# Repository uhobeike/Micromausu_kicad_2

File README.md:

# Micromausu_kicad_2
# move repository
## [InvetHub](https://inventhub.io/beike/Micromausu_2/tree/master/gekko?repoId=5f508c41b8c69c54c1f2025a&dirHash=&hash=25df0beb9022b2a77b5f545d1a530aec806a017b&path=gekko&size=undefined&isGitHub=true)

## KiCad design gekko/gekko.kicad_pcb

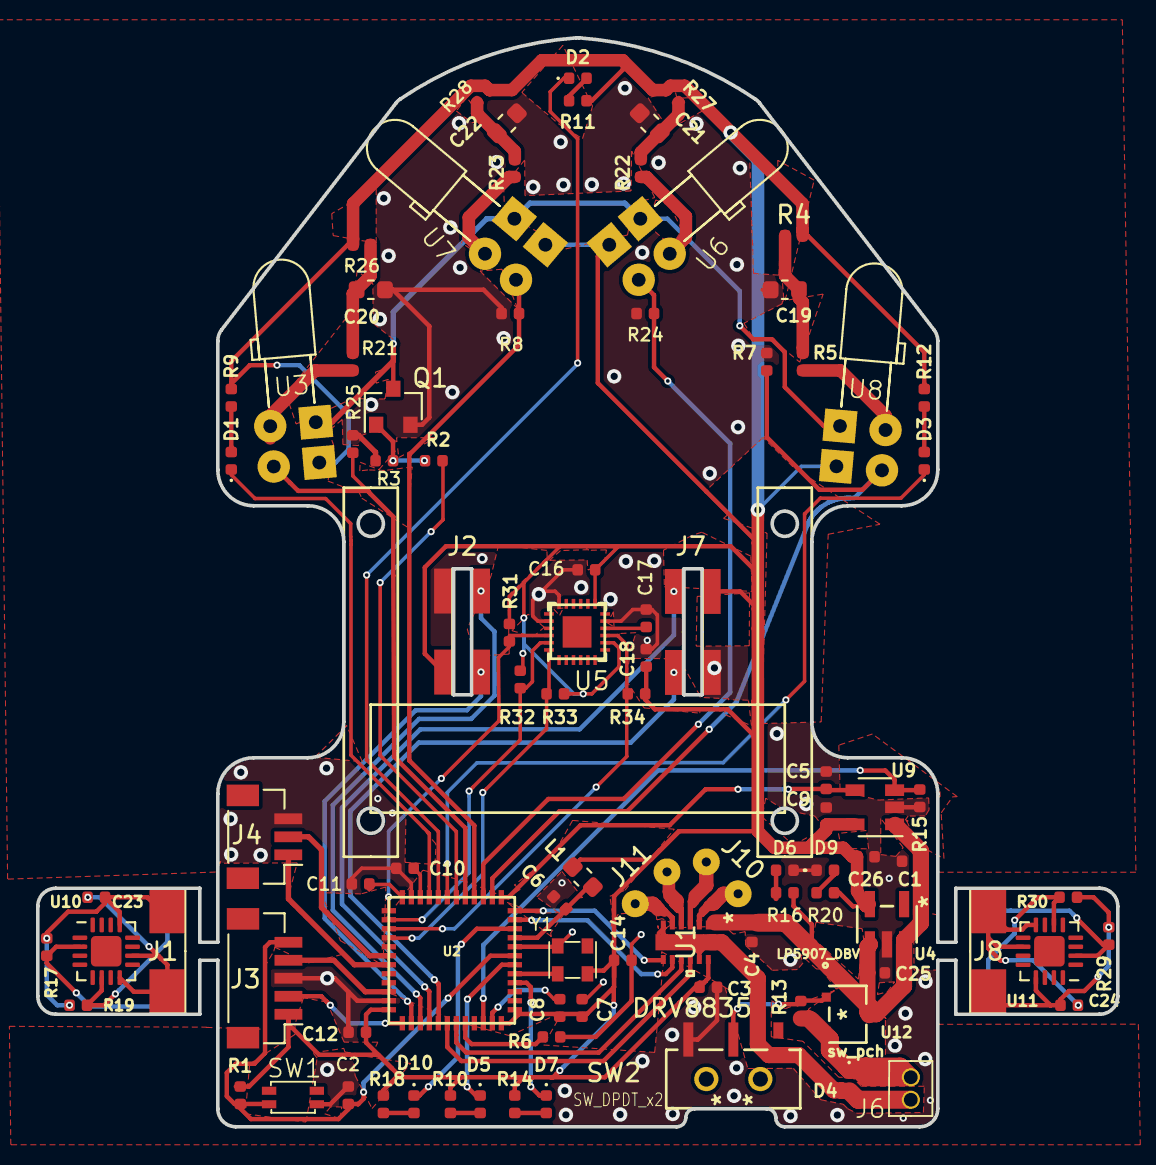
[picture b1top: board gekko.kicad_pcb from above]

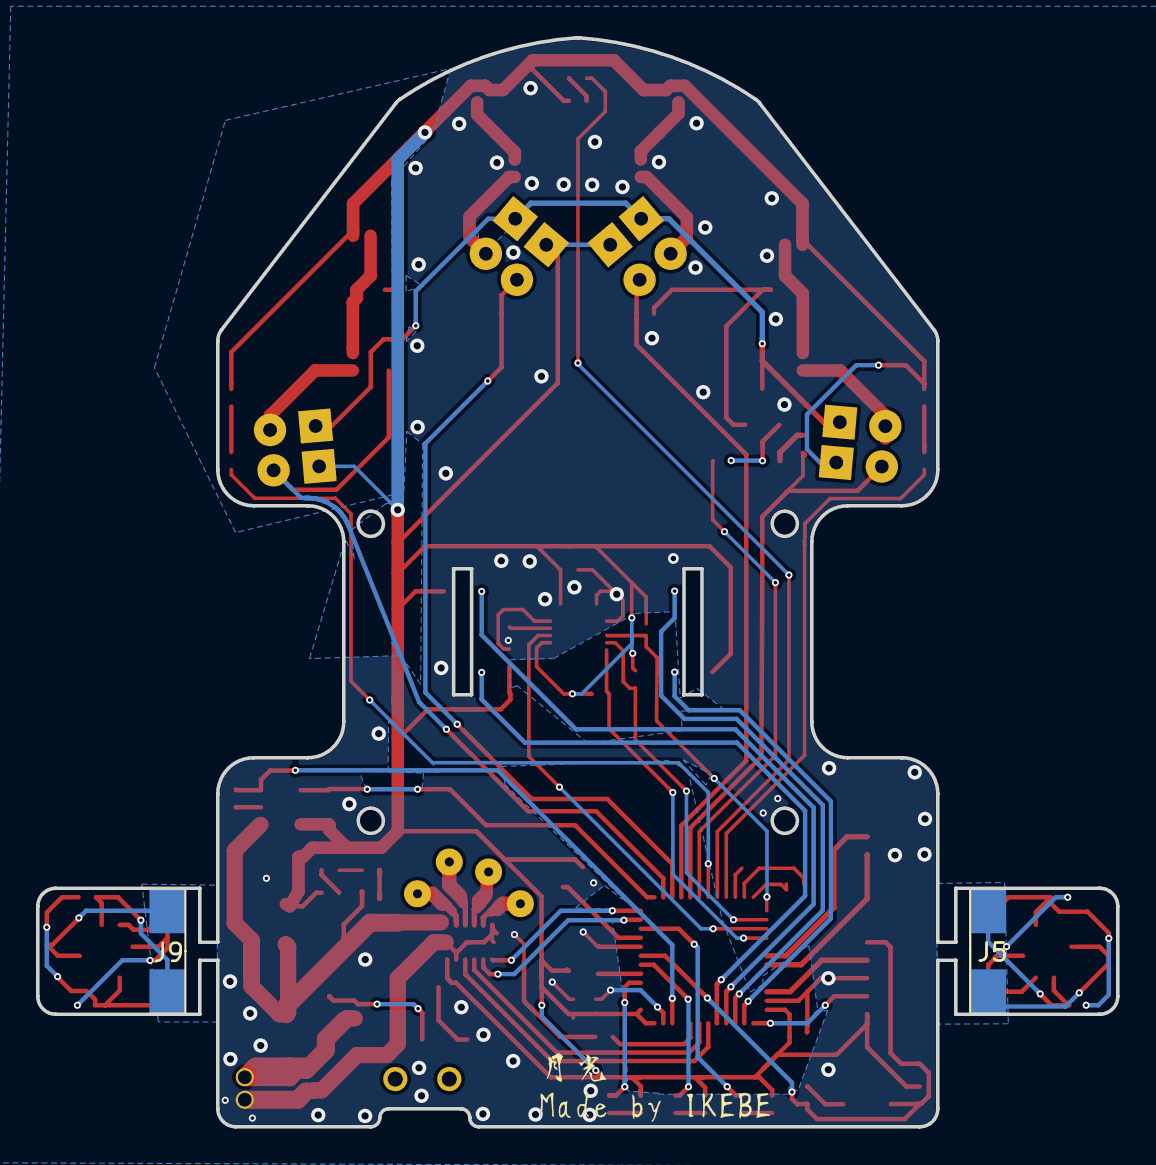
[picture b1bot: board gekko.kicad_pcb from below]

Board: 2 copper layers, 60.0 x 60.5 mm, 95 parts (2 on the bottom side), 71 nets.

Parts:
C1, C9, C23, C24, C25, C26: 1μ; C_0402_1005Metric
C2, C3, C4, C5, C6, C8, C11, C12, C14, C16, C17, C18: 0.1μ; C_0402_1005Metric
C7, C10: 10μ; C_0402_1005Metric
C19, C20, C21, C22: 47μ; C_0603_1608Metric
D1, D2, D3, D9: LED_RED; LED_0402_1005Metric
D4: D_TVS; D_0402_1005Metric
D5, D7, D10: LED_BLUE; LED_0402_1005Metric
D6: LED_GREEN; LED_0402_1005Metric
J1, J5, J8, J9: Conn_01x02_Male; enc_mount_bk_1
J2, J7: Conn_01x04_Female; enc_mount_fr_L
J3: Conn_01x05; JST_SH_BM05B-SRSS-TB_1x05-1MP_P1.00mm_Vertical
J4: Conn_01x03; JST_SH_BM03B-SRSS-TB_1x03-1MP_P1.00mm_Vertical
J6: Conn_01x02; 10114829-10102LF
J10, J11: Conn_01x02; motor_pad
L1: 330; L_0603_1608Metric
Q1: Q_NMOS_GSD; SOT-23
R1: 150k; R_0402_1005Metric
R2: 1.7; R_0402_1005Metric
R3, R6, R13, R15, R17, R19, R29, R30, R31, R32, R33, R34: 10k; R_0402_1005Metric
R4, R7, R8, R24, R25, R26, R27, R28: 1; R_0402_1005Metric
R5, R21, R22, R23: 2.49; R_0402_1005Metric
R9, R10, R11, R12, R14, R18: 330; R_0402_1005Metric
R16, R20: 165; R_0402_1005Metric
SW1: SW_Push_Dual_x2; EVP-BB2A9B000
SW2: SW_DPDT_x2; AYZ0102AGRLC
U1: DRV8835; DRV8835DSSR
U2: STM32F413CH6; STM32F411CEU6
U3, U6: LED_FOTR
U4: LP5907_DBV; LP5907MFX-3.3&slash_NOPB
U5: ICM20648
U7, U8: LED_FOTR; LED_FOTR_M
U9: RP124N334E-TR-FE; SOT-23-5
U10, U11: MA702GQ-P; QFN-16-1EP_3x3mm_P0.5mm_EP1.7x1.7mm
U12: sw_pch; SSM3J338R
Y1: Crystal_GND23; crystal

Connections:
+3.3V_L: C23.1, J1.1, R17.2, R19.2, U10.13
+3.3V_R: C24.1, J8.1, R29.2, R30.2, U11.13
+BATT: D4.1, J6.2, R13.1, U12.2
BATT_SW: C1.2, C4.2, C25.1, R16.1, U1.1, U4.1, U4.3, U9.1, U12.3
CROCK_IN: U2.5, Y1.3
CS_IMU: R31.2, U2.25, U5.22
DEBUG_LED1: D7.1, U2.4
DEBUG_LED2: D5.1, U2.6
DEBUG_LED3: D10.1, U2.10
DEBUG_LED4: D1.1, U2.21
DEBUG_LED5: D2.1, U2.20
DEBUG_LED6: D3.1, U2.19
GND: C1.1, C2.2, C3.2, C4.1, C5.2, C6.1, C7.2, C8.2, C9.2, C10.2, C11.2, C12.2, C14.2, C16.1, C17.1, C18.1, C19.2, C20.2, C21.2, C22.2, C25.2, C26.2, D4.2, D6.1, D9.1, J2.1, J3.3, J4.3, J6.1, J7.4, Q1.2, R3.1, R6.1, R7.2, R8.2, R15.1, R24.2, R25.2, SW1.1, SW2.1, U1.6, U1.11, U1.13, U1.14, U2.8, U2.23, U2.35, U2.47, U4.2, U5.11, U5.18, U5.20, U9.2, Y1.2
GND_L: C23.2, J1.2, U10.8, U10.10
GND_R: C24.2, J8.2, U11.8, U11.10
MISO_IMU: R34.2, U2.27, U5.9
MOSI_IMU: R33.2, U2.28, U5.24
MotorL_Foward: U1.7, U2.12
MotorL_Foward_Out: J11.1, U1.4
MotorL_Reverce: U1.8, U2.11
MotorL_Reverce_Out: J11.2, U1.5
MotorR_Foward: U1.9, U2.43
MotorR_Foward_Out: J10.1, U1.2
MotorR_Reverce: U1.10, U2.42
MotorR_Reverce_Out: J10.2, U1.3
NRST: C2.1, J3.5, R1.2, SW1.2, U2.7
unnamed: C6.2, L1.1, U2.9
unnamed: C10.1, U2.22
unnamed: C11.1, U2.24
unnamed: C17.2, U5.10
unnamed: C19.1, R4.1, R5.1
unnamed: C20.1, R21.1, R26.1
unnamed: C21.1, R22.1, R27.1
unnamed: C22.1, R23.1, R28.1
unnamed: D1.2, R9.1
unnamed: D2.2, R11.2
unnamed: D3.2, R12.1
unnamed: D5.2, R10.2
unnamed: D6.2, R16.2
unnamed: D7.2, R14.1
unnamed: D9.2, R20.2
unnamed: D10.2, R18.1
unnamed: Q1.1, R2.1, R3.2
unnamed: Q1.3, U3.4, U6.4, U7.4, U8.4
unnamed: R5.2, U8.3
unnamed: R6.2, U2.44
unnamed: R13.2, SW2.2, U12.1
unnamed: R21.2, U3.3
unnamed: R22.2, U7.3
unnamed: R23.2, U6.3
R_LED_PWM: R2.2, U2.18
SCK_IMU: R32.2, U2.26, U5.23
STLINK_TCK: J3.2, U2.37
STLINK_TMS: J3.4, U2.34
USART_RX: J4.1, U2.31
USART_TX: J4.2, U2.30
battery_sw_CE: R15.2, U2.46, U9.3
battery_wt: C5.1, U2.13, U9.4
battery_wt_vout: C3.1, C7.1, C8.1, C9.1, C12.1, C14.1, C16.2, C18.2, C26.1, J2.2, J3.1, J7.3, L1.2, R1.1, R4.2, R9.2, R10.1, R11.1, R12.2, R14.2, R18.2, R20.1, R26.2, R27.2, R28.2, R31.1, R32.1, R33.1, R34.1, U1.12, U2.1, U2.36, U2.48, U3.1, U4.5, U5.8, U5.13, U6.1, U7.1, U8.1, U9.5, Y1.4
encL_1_EXTI: J2.3, U2.39
encL_1_EXTI_cn: J5.1, R17.1, U10.2
encL_2_EXTI: J2.4, U2.38
encL_2_EXTI_cn: J5.2, R19.1, U10.6
encR_1_EXTI: J7.2, U2.41
encR_1_EXTI_cn: J9.1, R29.1, U11.2
encR_2_EXTI: J7.1, U2.40
encR_2_EXTI_cn: J9.2, R30.1, U11.6
sens_L: R8.1, U2.16, U6.2
sens_LL: R25.1, U2.17, U3.2
sens_R: R24.1, U2.15, U7.2
sens_RR: R7.1, U2.14, U8.2

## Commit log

2019-11-02 first touch
2019-11-03 haisenmae
2019-11-04 finish
2019-11-05 finish 2
2019-11-05 finish 3
2019-11-05 finish 4
2019-11-05 finish 5
2019-11-05 beta finish
2019-11-07 rename
2020-02-10 one-finish
2020-03-30 new_re
2020-04-07 betaGND
2020-04-07 betaGND_B
2020-04-25 hattyu_v2
2020-05-02 RE_patern
2020-05-02 RE_patern_finish
2020-05-03 RE_patern_finish_2
2020-05-03 RE_beta_finish
2020-09-03 For the time being

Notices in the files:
parts and their libraries:
Copyright 2016 Accelerated Designs. All rights reserved.
